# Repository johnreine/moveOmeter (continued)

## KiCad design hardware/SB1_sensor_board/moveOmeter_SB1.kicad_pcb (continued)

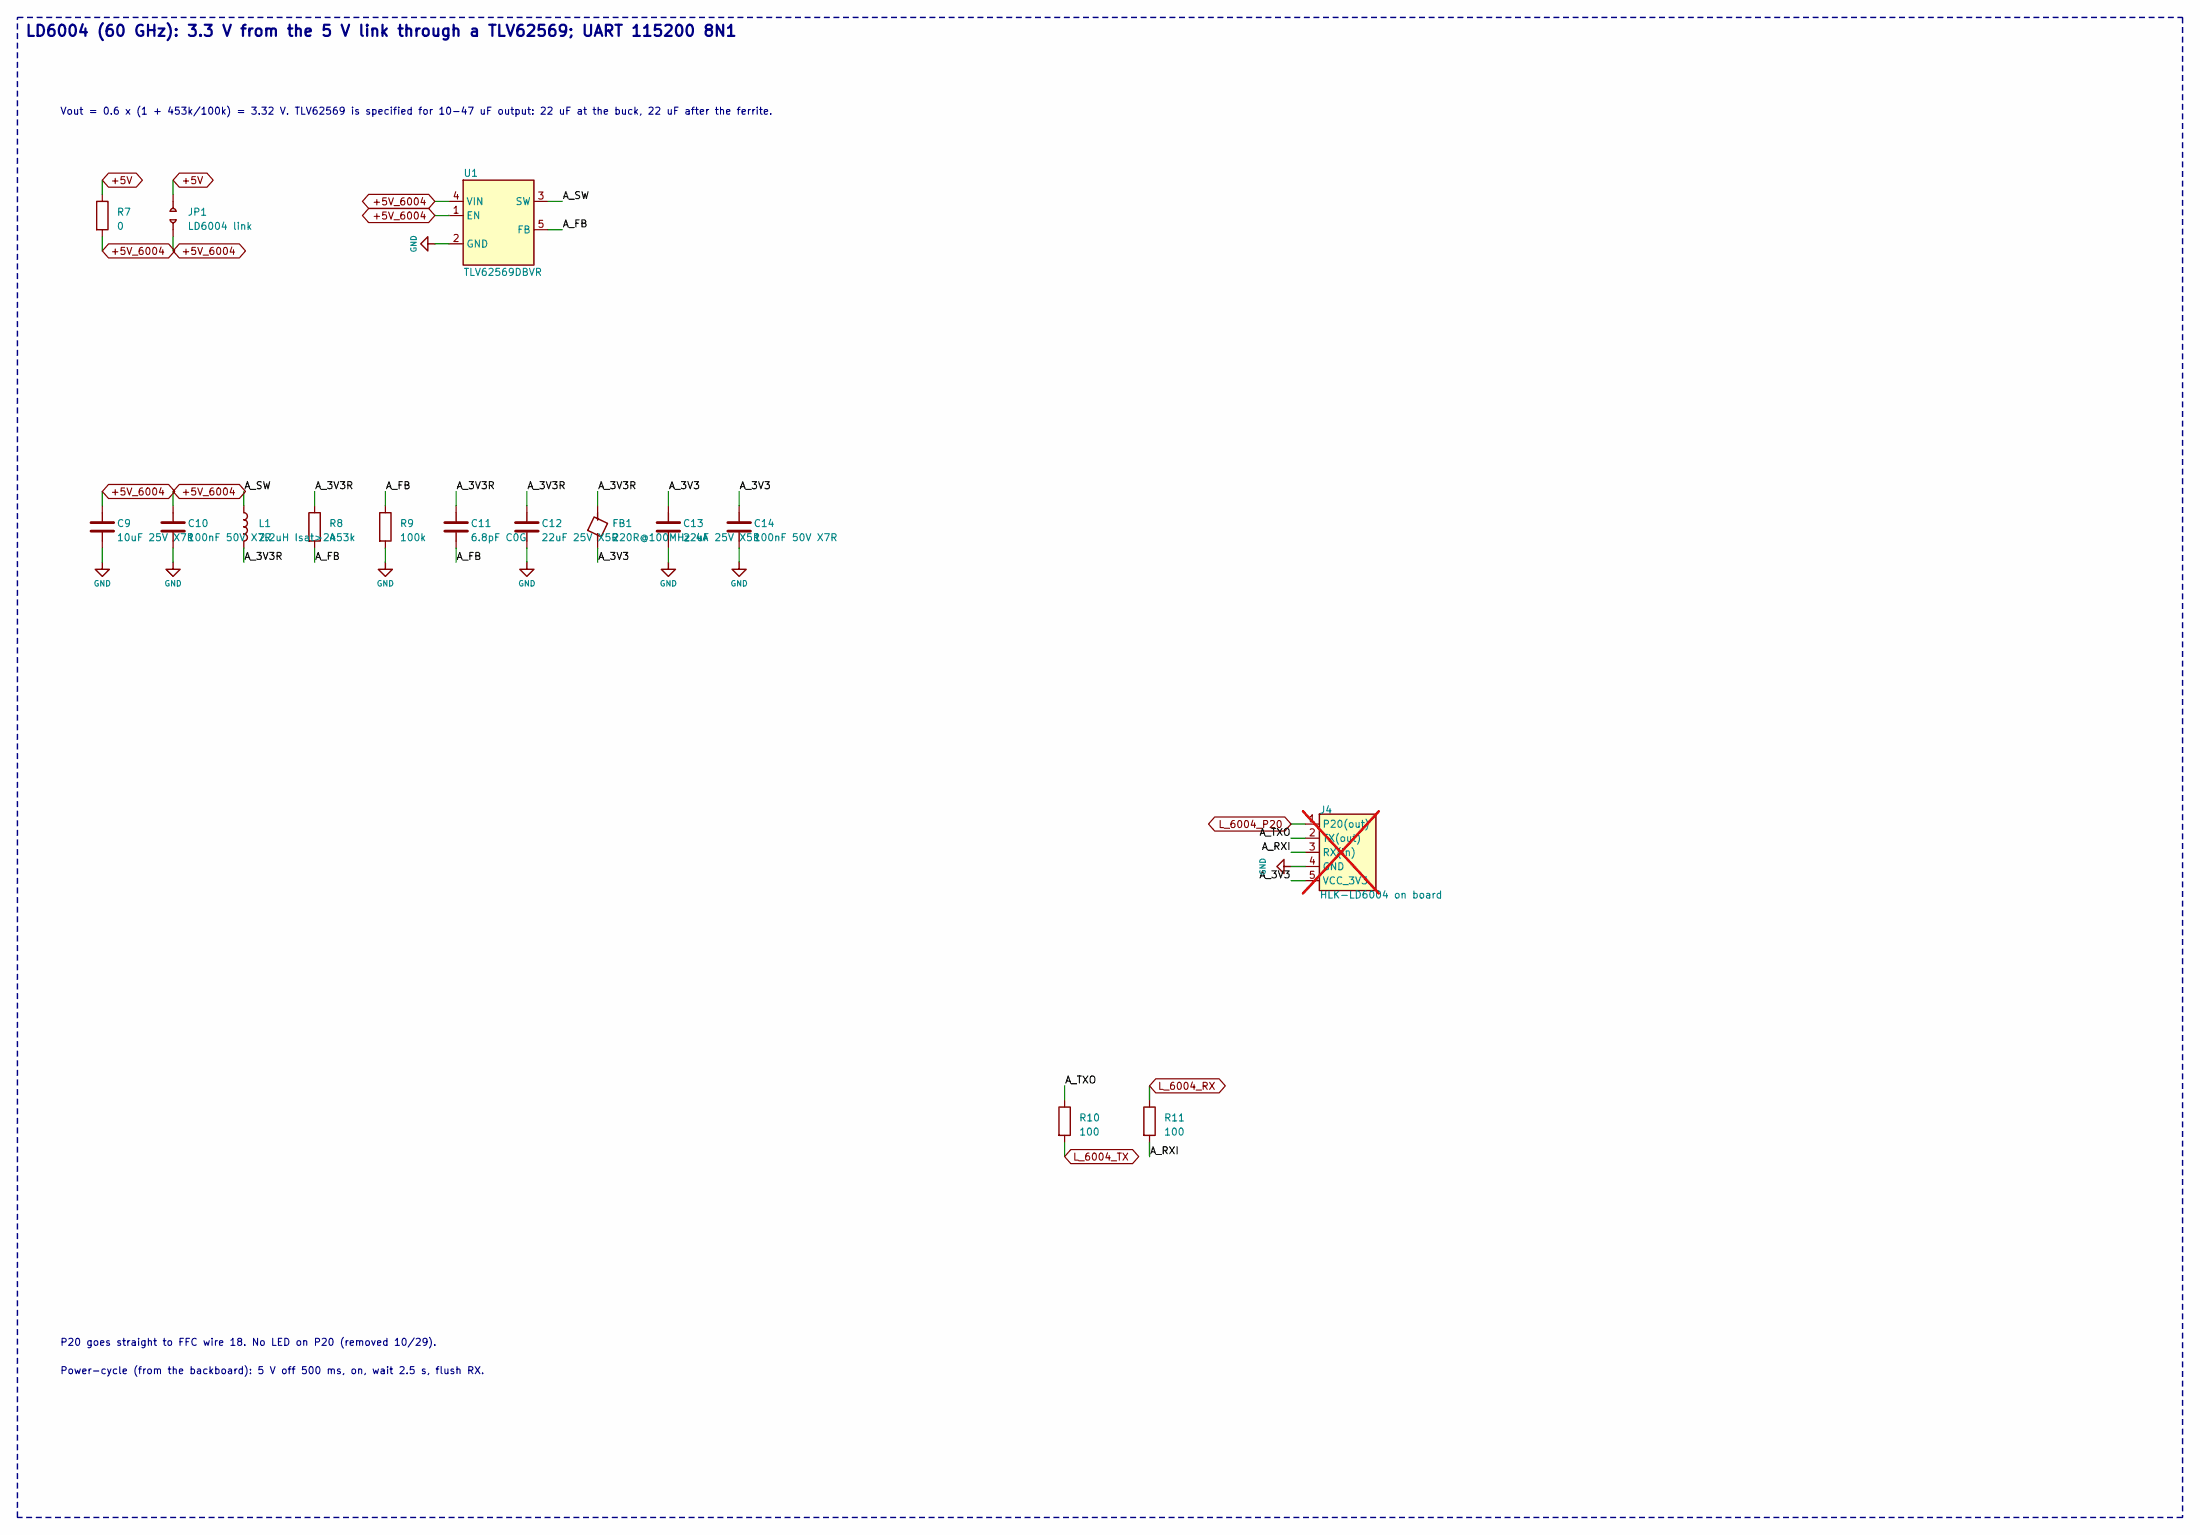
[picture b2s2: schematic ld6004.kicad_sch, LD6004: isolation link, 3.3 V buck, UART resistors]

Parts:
C9: 10uF 25V X7R; C_1210_3225Metric_Pad1.33x2.70mm_HandSolder; MPN GRM32DR71E106KA12L
C10, C14: 100nF 50V X7R; C_1206_3216Metric_Pad1.33x1.80mm_HandSolder; MPN CL31B104KBCNNNC
C11: 6.8pF C0G; C_1206_3216Metric_Pad1.33x1.80mm_HandSolder; MPN CC1206CRNPO9BN6R8
C12, C13: 22uF 25V X5R; C_1210_3225Metric_Pad1.33x2.70mm_HandSolder; MPN GRM32ER61E226KE15L
FB1: 220R@100MHz 4A; L_1206_3216Metric_Pad1.22x1.90mm_HandSolder; MPN LSMGA321616T221NG
J4: HLK-LD6004 on board; HLK-LD6004_Module_2x1x05_P1.27mm; MPN LPPB051NFFN-RC; not fitted
JP1: LD6004 link; SolderJumper-2_P1.3mm_Open_RoundedPad1.0x1.5mm
L1: 2.2uH Isat>2A; L_Bourns-SRN4018; MPN SRN4018-2R2M
R7: 0; R_1206_3216Metric_Pad1.30x1.75mm_HandSolder; MPN RC1206JR-070RL
R8: 453k; R_1206_3216Metric_Pad1.30x1.75mm_HandSolder; MPN RC1206FR-07453KL
R9: 100k; R_1206_3216Metric_Pad1.30x1.75mm_HandSolder; MPN RC1206FR-07100KL
R10, R11: 100; R_1206_3216Metric_Pad1.30x1.75mm_HandSolder; MPN RC1206FR-07100RL
U1: TLV62569DBVR; SOT-23-5; MPN TLV62569DBVR

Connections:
+5V: JP1.1, R7.1; also elsewhere on the board
+5V_6004: C9.1, C10.1, JP1.2, R7.2, U1.1 (EN), U1.4 (VIN)
/LD6004/A_3V3: C13.1, C14.1, FB1.2, J4.5 (VCC_3V3)
/LD6004/A_3V3R: C11.1, C12.1, FB1.1, L1.2, R8.1
/LD6004/A_FB: C11.2, R8.2, R9.1, U1.5 (FB)
/LD6004/A_RXI: J4.3 (RX(in)), R11.2
/LD6004/A_SW: L1.1, U1.3 (SW)
/LD6004/A_TXO: J4.2 (TX(out)), R10.1
GND: C9.2, C10.2, C12.2, C13.2, C14.2, J4.4 (GND), R9.2, U1.2 (GND); also elsewhere on the board
L_6004_P20: J4.1 (P20(out)); also elsewhere on the board
L_6004_RX: R11.1; also elsewhere on the board
L_6004_TX: R10.2; also elsewhere on the board

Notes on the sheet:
LD6004 (60 GHz): 3.3 V from the 5 V link through a TLV62569; UART 115200 8N1
Power-cycle (from the backboard): 5 V off 500 ms, on, wait 2.5 s, flush RX.
Vout = 0.6 x (1 + 453k/100k) = 3.32 V. TLV62569 is specified for 10-47 uF output: 22 uF at the buck, 22 uF after the ferrite.
P20 goes straight to FFC wire 18. No LED on P20 (removed 10/29).

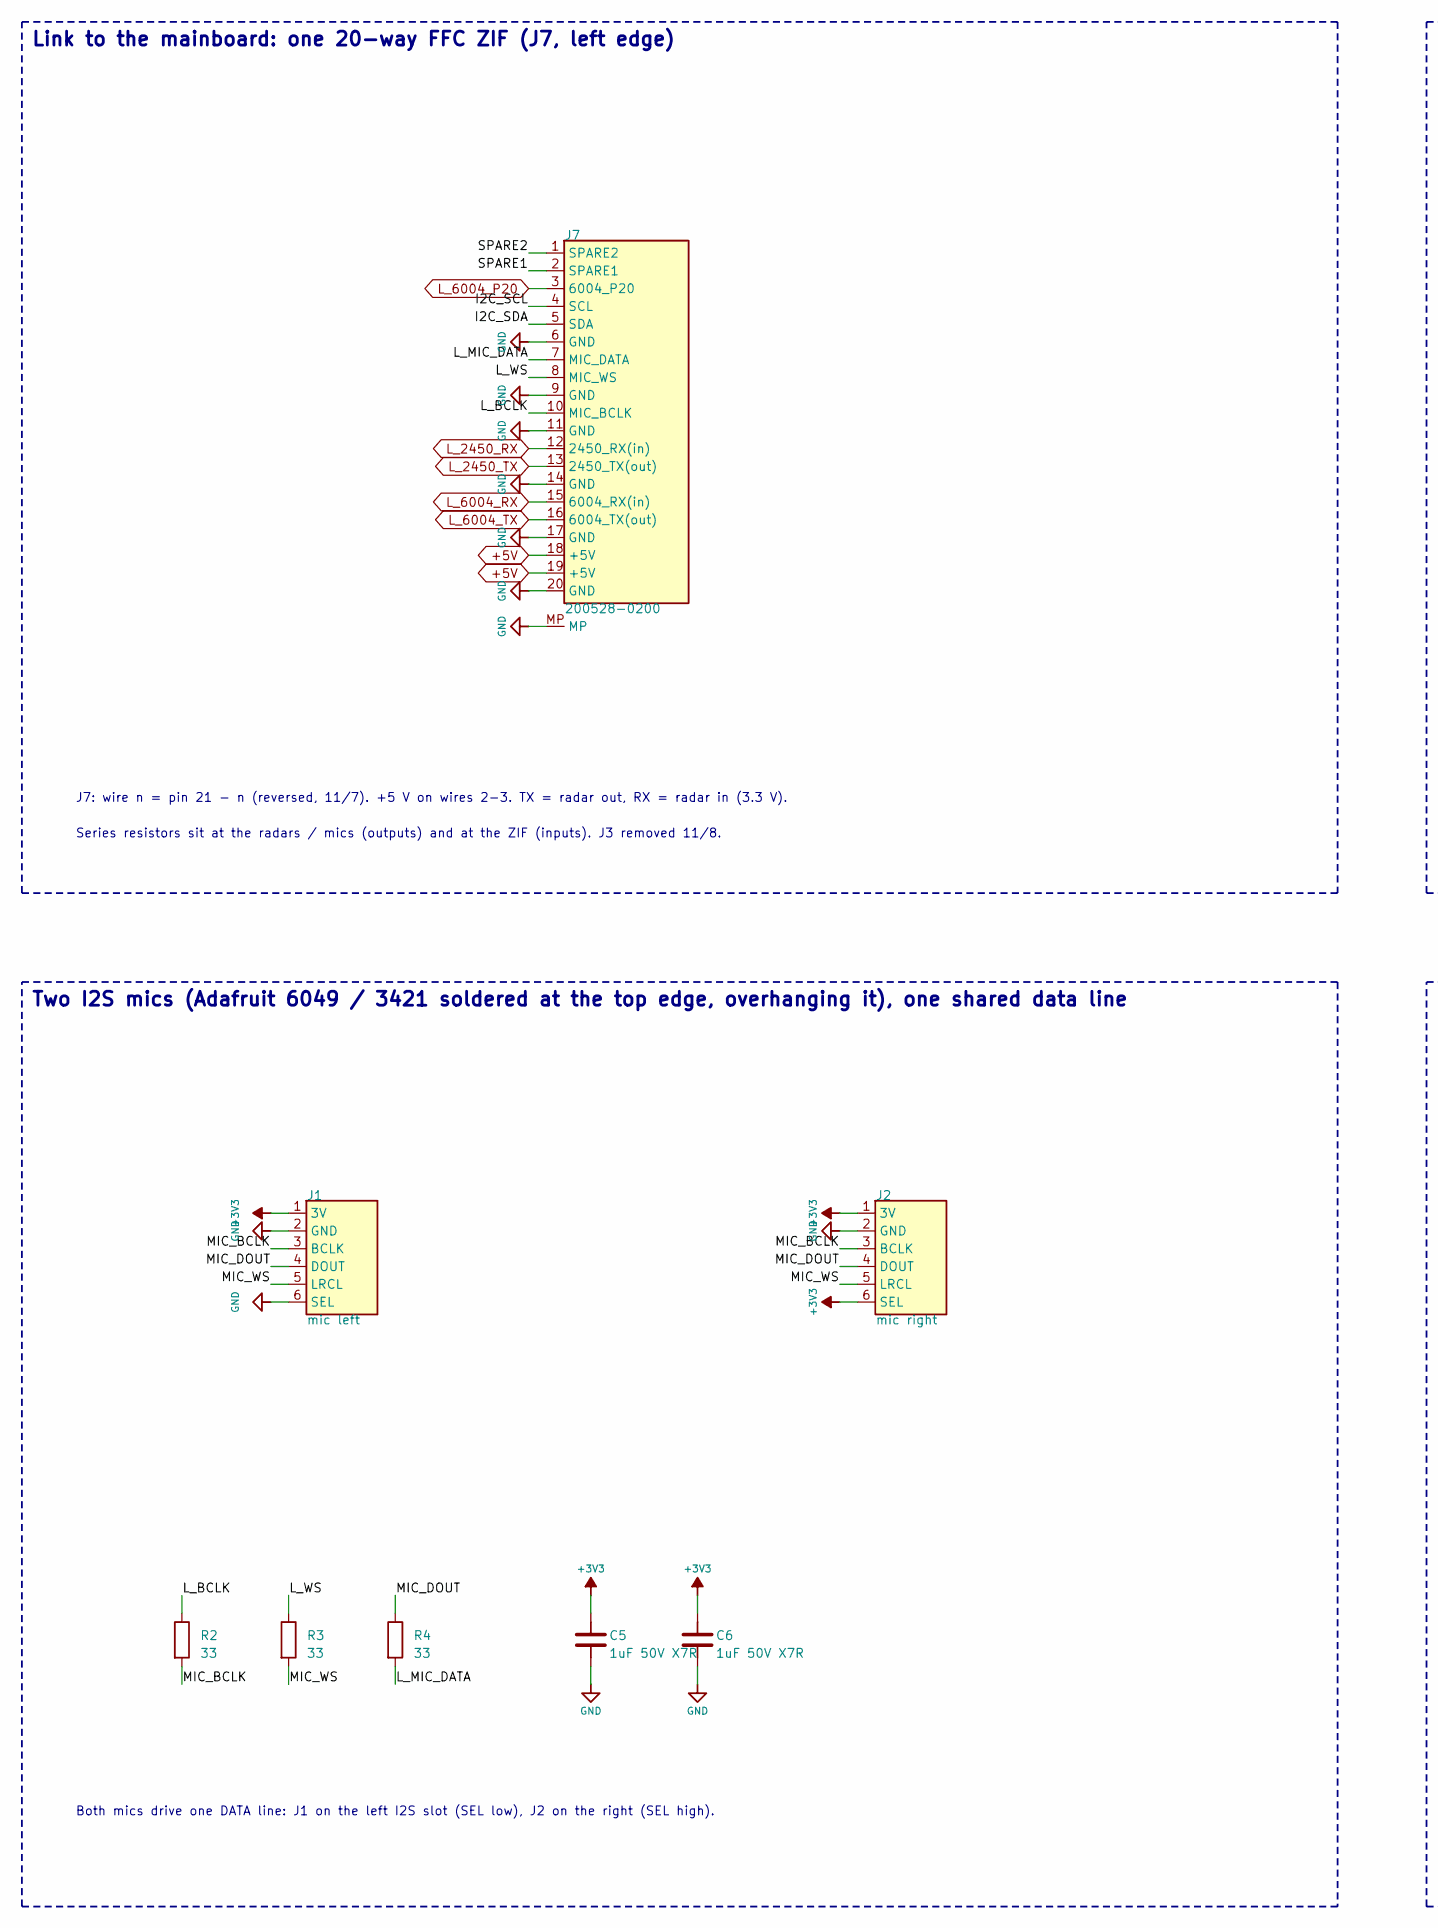
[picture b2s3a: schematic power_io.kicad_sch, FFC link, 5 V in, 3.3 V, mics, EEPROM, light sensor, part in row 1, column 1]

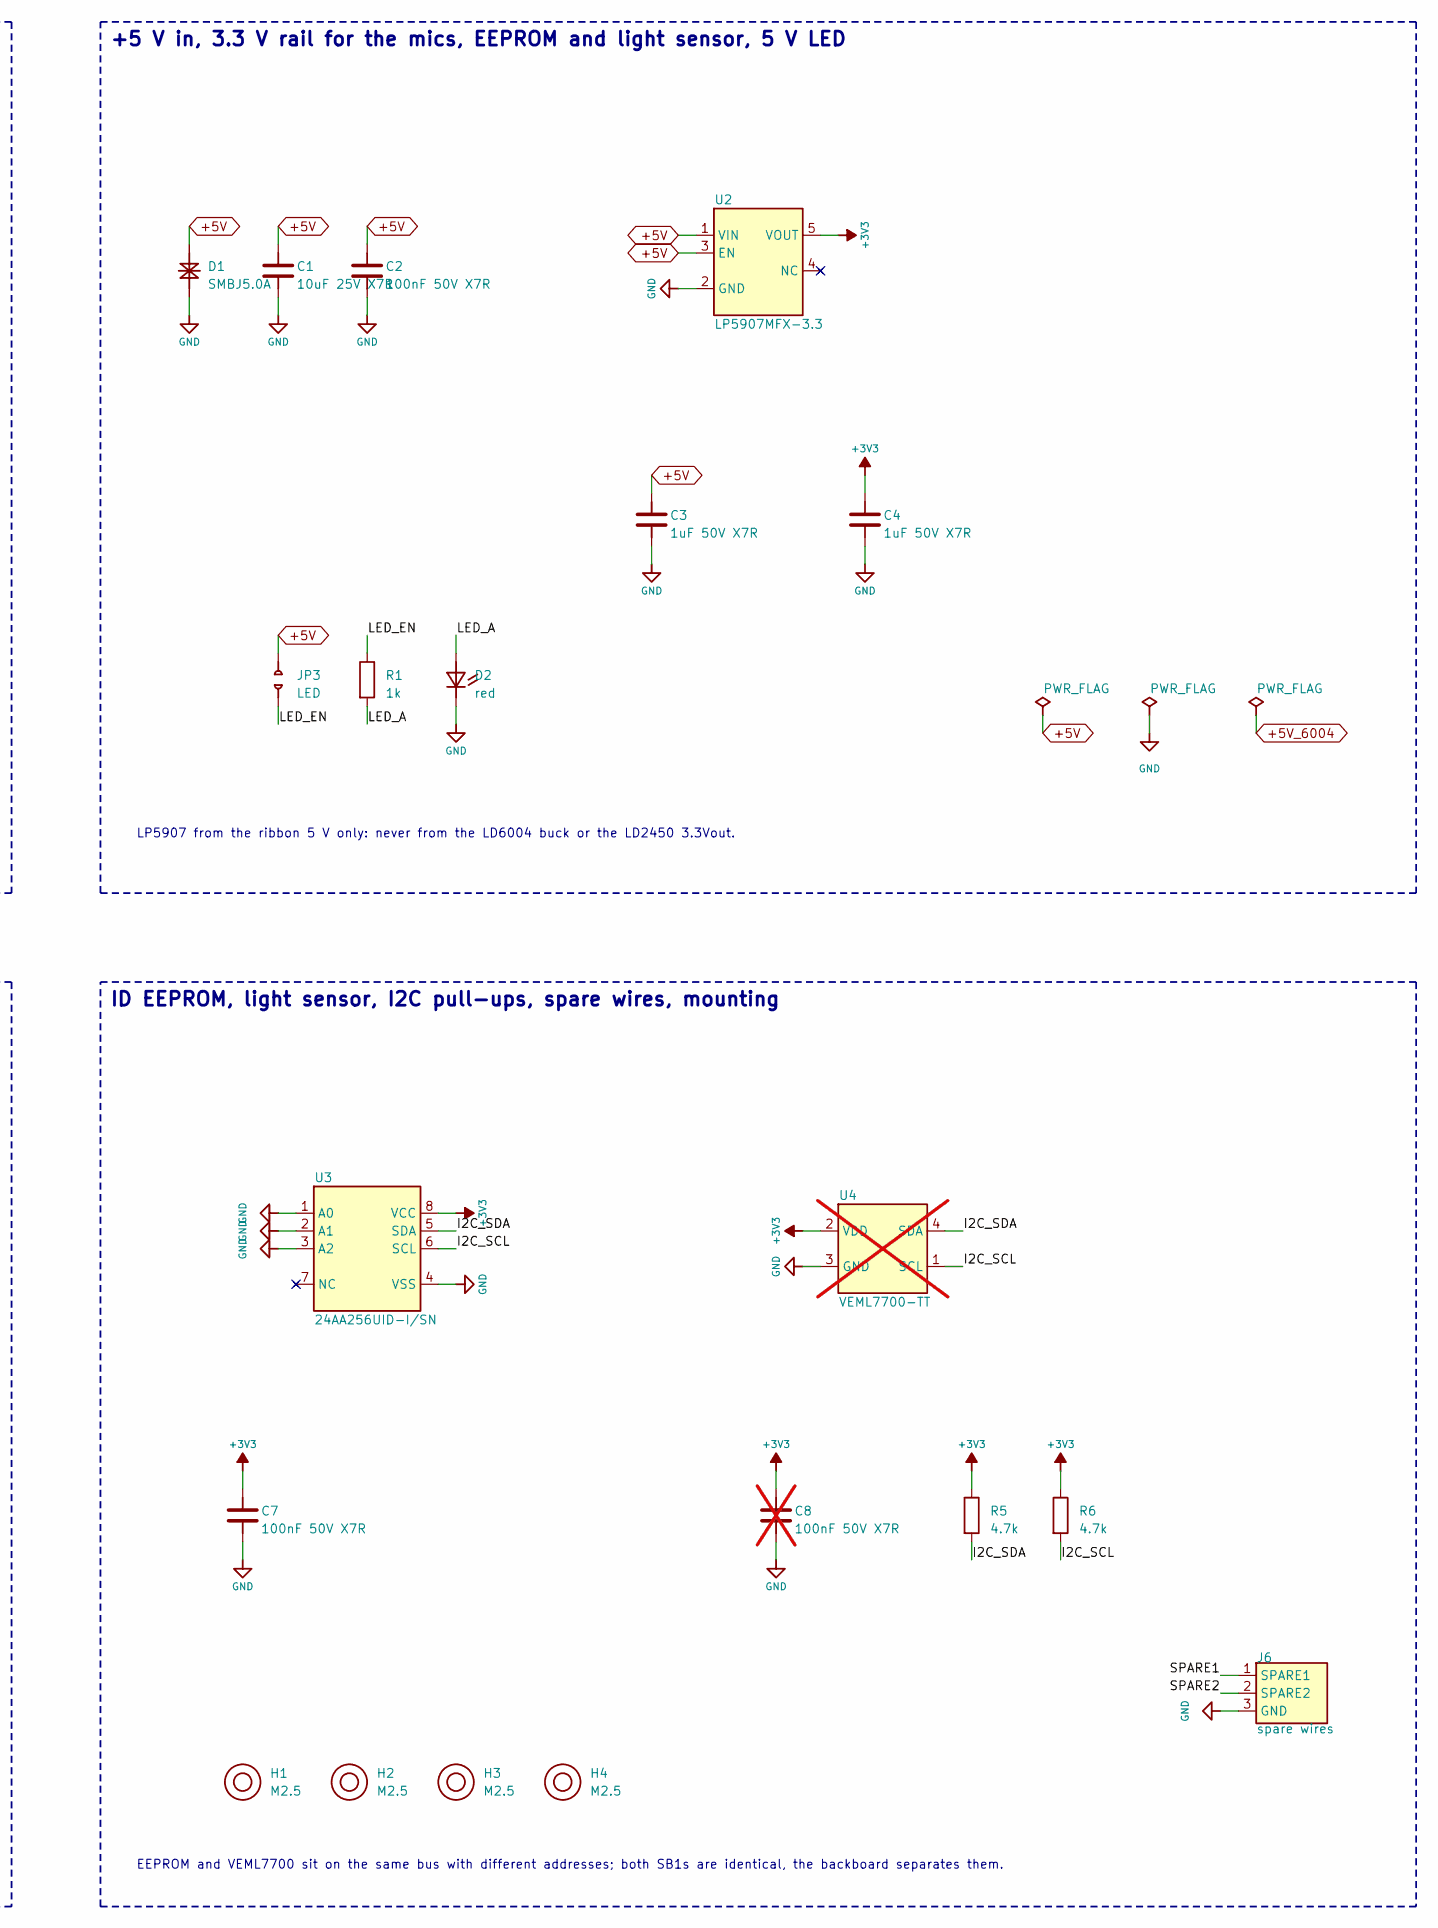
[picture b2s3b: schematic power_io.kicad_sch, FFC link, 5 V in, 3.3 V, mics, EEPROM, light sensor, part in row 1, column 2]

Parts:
C1: 10uF 25V X7R; C_1210_3225Metric_Pad1.33x2.70mm_HandSolder; MPN GRM32DR71E106KA12L
C2, C7: 100nF 50V X7R; C_1206_3216Metric_Pad1.33x1.80mm_HandSolder; MPN CL31B104KBCNNNC
C3, C4, C5, C6: 1uF 50V X7R; C_1206_3216Metric_Pad1.33x1.80mm_HandSolder; MPN CC1206KKX7R9BB105
C8: 100nF 50V X7R; C_1206_3216Metric_Pad1.33x1.80mm_HandSolder; MPN CL31B104KBCNNNC; not fitted
D1: SMBJ5.0A; D_SMB_Handsoldering; MPN SMBJ5.0A
D2: red; LED_1206_3216Metric_Pad1.42x1.75mm_HandSolder; MPN LTST-C150KRKT
H1, H2, H3, H4: M2.5; MountingHole_2.7mm_M2.5_KeepOut
J1: mic left; Adafruit_I2S_Mic_Breakout_1x06_Overhang_Back; MPN 6049
J2: mic right; Adafruit_I2S_Mic_Breakout_1x06_Overhang_Back; MPN 6049
J6: spare wires; PinHeader_1x03_P2.54mm_Vertical; MPN PEC03SAAN
J7: 200528-0200; Molex_200528-0200_1x20-1MP_P1.00mm_Horizontal; MPN 200528-0200
JP3: LED; SolderJumper-2_P1.3mm_Open_RoundedPad1.0x1.5mm
R1: 1k; R_1206_3216Metric_Pad1.30x1.75mm_HandSolder; MPN RC1206FR-071KL
R2, R3, R4: 33; R_1206_3216Metric_Pad1.30x1.75mm_HandSolder; MPN RC1206FR-0733RL
R5, R6: 4.7k; R_1206_3216Metric_Pad1.30x1.75mm_HandSolder; MPN RC1206FR-074K7L
U2: LP5907MFX-3.3; SOT-23-5; MPN LP5907MFX-3.3/NOPB
U3: 24AA256UID-I/SN; SOIC-8_3.9x4.9mm_P1.27mm; MPN 24AA256UID-I/SN
U4: VEML7700-TT; Vishay_VEML7700_TopView; MPN VEML7700-TT; not fitted

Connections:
+3V3: C4.1, C5.1, C6.1, C7.1, C8.1, J1.1 (3V), J2.1 (3V), J2.6 (SEL), R5.1, R6.1, U2.5 (VOUT), U3.8 (VCC), U4.2 (VDD)
+5V: C1.1, C2.1, C3.1, D1.1 (K), J7.18 (+5V), J7.19 (+5V), JP3.1, U2.1 (VIN), U2.3 (EN); also elsewhere on the board
/Power_IO/I2C_SCL: J7.4 (SCL), R6.2, U3.6 (SCL), U4.1 (SCL)
/Power_IO/I2C_SDA: J7.5 (SDA), R5.2, U3.5 (SDA), U4.4 (SDA)
/Power_IO/LED_A: D2.2 (A), R1.2
/Power_IO/LED_EN: JP3.2, R1.1
/Power_IO/L_BCLK: J7.10 (MIC_BCLK), R2.1
/Power_IO/L_MIC_DATA: J7.7 (MIC_DATA), R4.2
/Power_IO/L_WS: J7.8 (MIC_WS), R3.1
/Power_IO/MIC_BCLK: J1.3 (BCLK), J2.3 (BCLK), R2.2
/Power_IO/MIC_DOUT: J1.4 (DOUT), J2.4 (DOUT), R4.1
/Power_IO/MIC_WS: J1.5 (LRCL), J2.5 (LRCL), R3.2
/Power_IO/SPARE1: J6.1 (SPARE1), J7.2 (SPARE1)
/Power_IO/SPARE2: J6.2 (SPARE2), J7.1 (SPARE2)
GND: C1.2, C2.2, C3.2, C4.2, C5.2, C6.2, C7.2, C8.2, D1.2 (A), D2.1 (K), J1.2 (GND), J1.6 (SEL), J2.2 (GND), J6.3 (GND), J7.6 (GND), J7.9 (GND), J7.11 (GND), J7.14 (GND), J7.17 (GND), J7.20 (GND), J7.MP, U2.2 (GND), U3.1 (A0), U3.2 (A1), U3.3 (A2), U3.4 (VSS), U4.3 (GND); also elsewhere on the board
L_2450_RX: J7.12 (2450_RX(in)); also elsewhere on the board
L_2450_TX: J7.13 (2450_TX(out)); also elsewhere on the board
L_6004_P20: J7.3 (6004_P20); also elsewhere on the board
L_6004_RX: J7.15 (6004_RX(in)); also elsewhere on the board
L_6004_TX: J7.16 (6004_TX(out)); also elsewhere on the board

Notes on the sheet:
ID EEPROM, light sensor, I2C pull-ups, spare wires, mounting
LP5907 from the ribbon 5 V only: never from the LD6004 buck or the LD2450 3.3Vout.
EEPROM and VEML7700 sit on the same bus with different addresses; both SB1s are identical, the backboard separates them.
J7: wire n = pin 21 - n (reversed, 11/7). +5 V on wires 2-3. TX = radar out, RX = radar in (3.3 V).
+5 V in, 3.3 V rail for the mics, EEPROM and light sensor, 5 V LED
Series resistors sit at the radars / mics (outputs) and at the ZIF (inputs). J3 removed 11/8.
Both mics drive one DATA line: J1 on the left I2S slot (SEL low), J2 on the right (SEL high).
Two I2S mics (Adafruit 6049 / 3421 soldered at the top edge, overhanging it), one shared data line
Link to the mainboard: one 20-way FFC ZIF (J7, left edge)

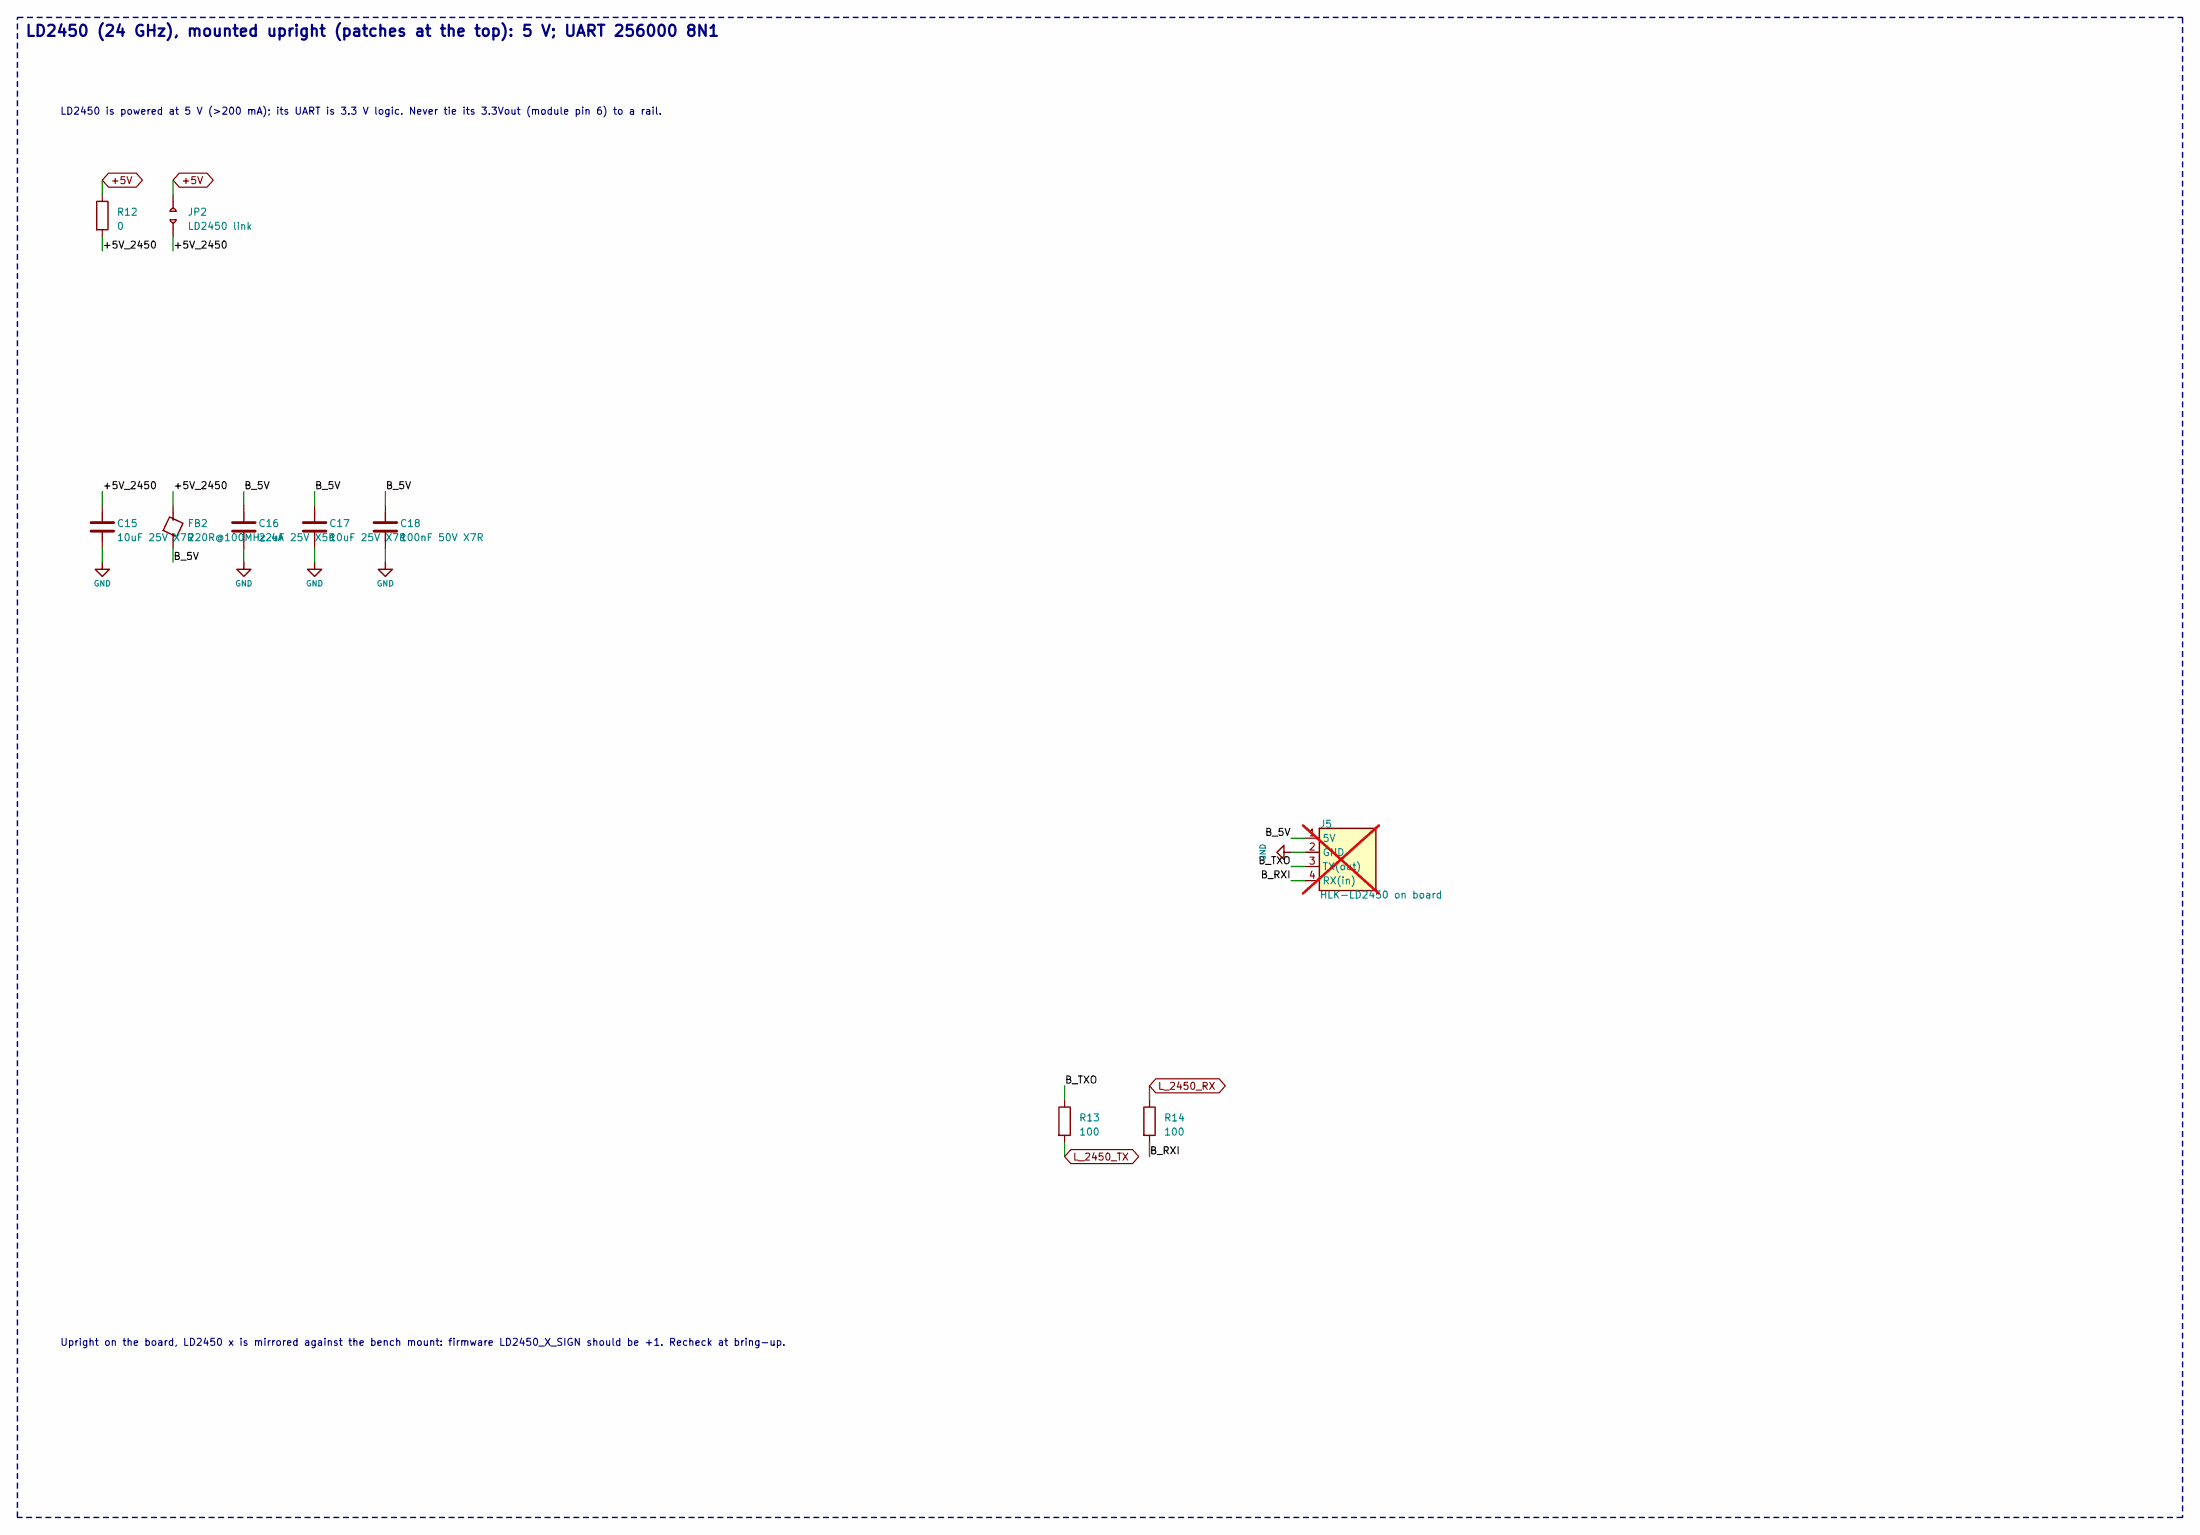
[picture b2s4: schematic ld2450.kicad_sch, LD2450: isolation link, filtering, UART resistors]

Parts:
C15, C17: 10uF 25V X7R; C_1210_3225Metric_Pad1.33x2.70mm_HandSolder; MPN GRM32DR71E106KA12L
C16: 22uF 25V X5R; C_1210_3225Metric_Pad1.33x2.70mm_HandSolder; MPN GRM32ER61E226KE15L
C18: 100nF 50V X7R; C_1206_3216Metric_Pad1.33x1.80mm_HandSolder; MPN CL31B104KBCNNNC
FB2: 220R@100MHz 4A; L_1206_3216Metric_Pad1.22x1.90mm_HandSolder; MPN LSMGA321616T221NG
J5: HLK-LD2450 on board; HLK-LD2450_Module_2x04_P2.00mm; MPN NPPN042AFCN-RC; not fitted
JP2: LD2450 link; SolderJumper-2_P1.3mm_Open_RoundedPad1.0x1.5mm
R12: 0; R_1206_3216Metric_Pad1.30x1.75mm_HandSolder; MPN RC1206JR-070RL
R13, R14: 100; R_1206_3216Metric_Pad1.30x1.75mm_HandSolder; MPN RC1206FR-07100RL

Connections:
+5V: JP2.1, R12.1; also elsewhere on the board
/LD2450/+5V_2450: C15.1, FB2.1, JP2.2, R12.2
/LD2450/B_5V: C16.1, C17.1, C18.1, FB2.2, J5.1 (5V)
/LD2450/B_RXI: J5.4 (RX(in)), R14.2
/LD2450/B_TXO: J5.3 (TX(out)), R13.1
GND: C15.2, C16.2, C17.2, C18.2, J5.2 (GND); also elsewhere on the board
L_2450_RX: R14.1; also elsewhere on the board
L_2450_TX: R13.2; also elsewhere on the board

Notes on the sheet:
LD2450 is powered at 5 V (>200 mA); its UART is 3.3 V logic. Never tie its 3.3Vout (module pin 6) to a rail.
LD2450 (24 GHz), mounted upright (patches at the top): 5 V; UART 256000 8N1
Upright on the board, LD2450 x is mirrored against the bench mount: firmware LD2450_X_SIGN should be +1. Recheck at bring-up.

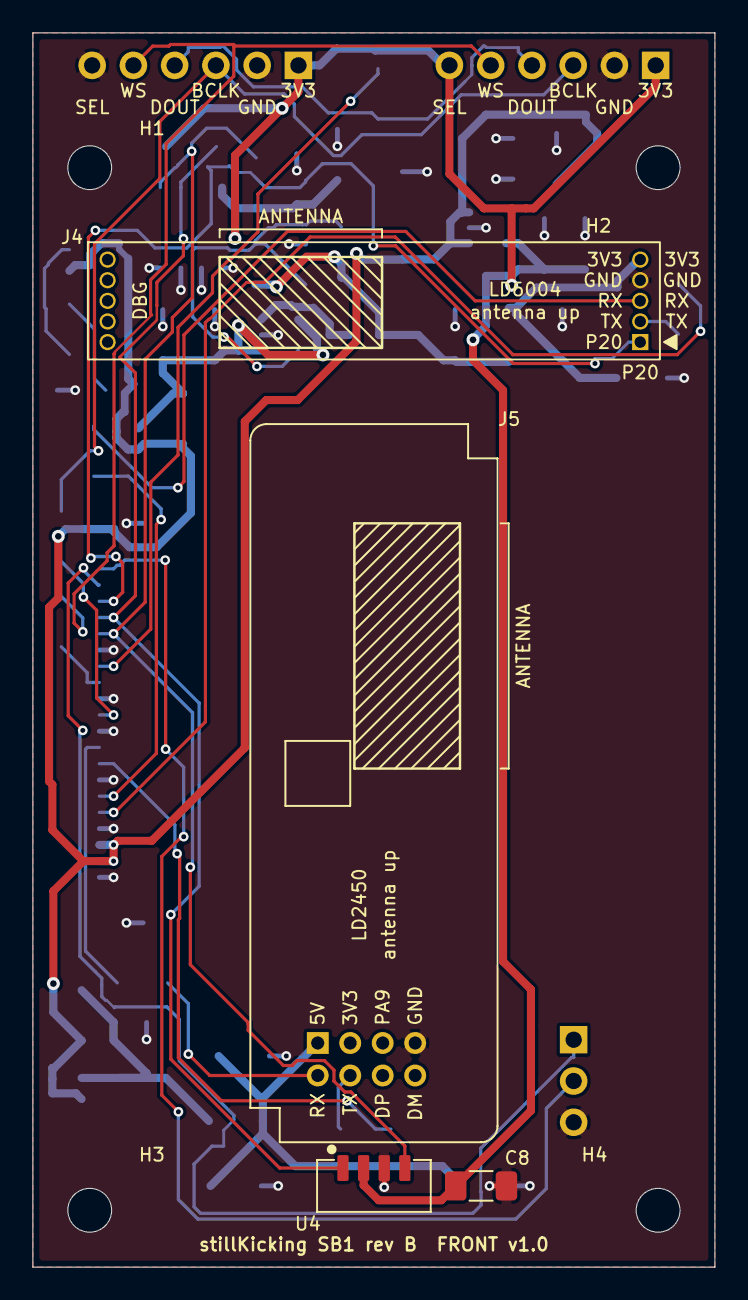
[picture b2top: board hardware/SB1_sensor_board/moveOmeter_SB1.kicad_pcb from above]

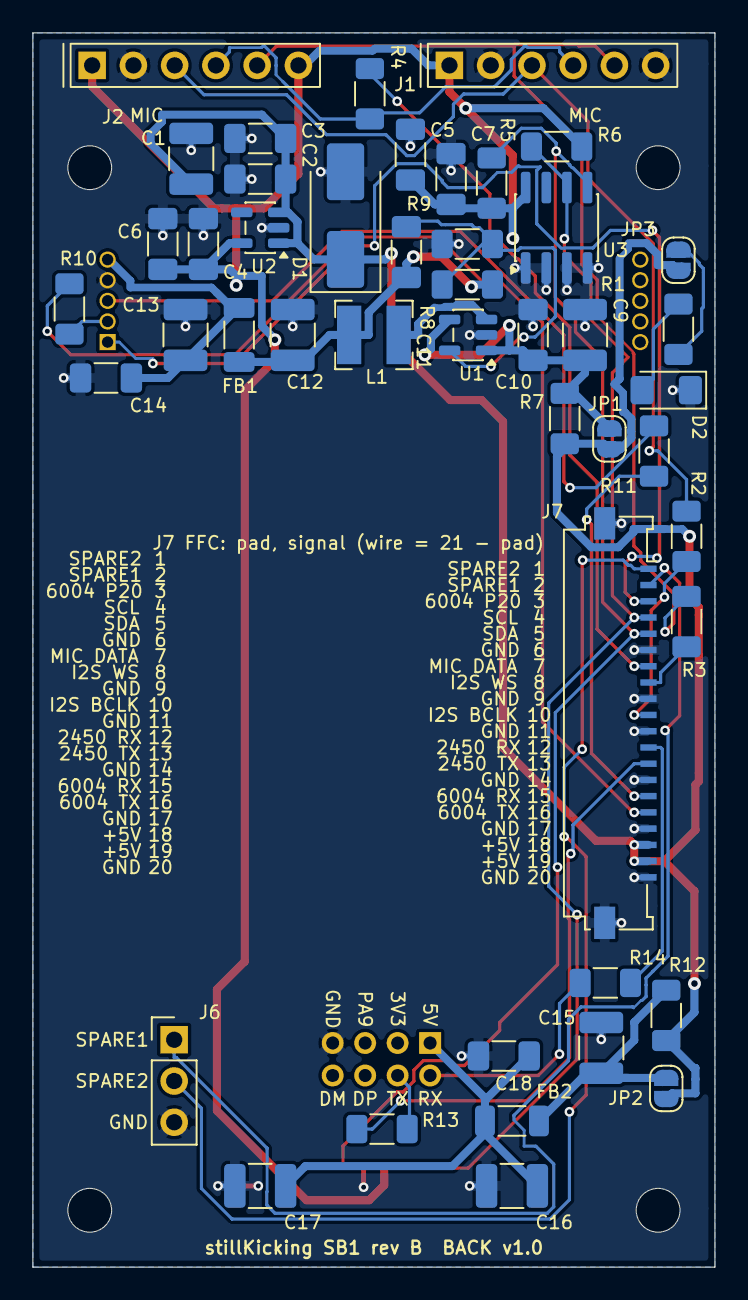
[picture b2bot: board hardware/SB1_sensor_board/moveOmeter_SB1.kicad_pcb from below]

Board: 4 copper layers, 42.0 x 76.0 mm, 54 parts (46 on the bottom side), 31 nets.

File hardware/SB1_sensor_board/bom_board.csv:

Refs,Qty per board,Value,Manufacturer,MPN,Footprint,Fit,Vendor,Vendor Part #,"Price (qty 1, USD)",Ext price per board (USD),Vendor Link,Datasheet
"C1, C9, C15, C17",4,10uF 25V X7R,Murata,GRM32DR71E106KA12L,C_1210_3225Metric_Pad1.33x2.70mm_HandSolder,,DigiKey,490-1867-1-ND,0.98,3.92,https://www.digikey.com/en/products/detail/murata-electronic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,https://pim.murata.com/asset/pim4/ceramicCapacitorSMD/GRM32D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
"C2, C7, C10, C14, C18",5,100nF 50V X7R,Samsung,CL31B104KBCNNNC,C_1206_3216Metric_Pad1.33x1.80mm_HandSolder,,DigiKey,1276-1017-1-ND,0.14,0.7,https://www.digikey.com/en/products/detail/samsung-electro-m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,https://weblib.samsungsem.com/mlcc/mlcc-ec-data-sheet.do?par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
"C3, C4, C5, C6",4,1uF 50V X7R,Yageo,CC1206KKX7R9BB105,C_1206_3216Metric_Pad1.33x1.80mm_HandSolder,,DigiKey,311-1963-1-ND,0.36,1.44,https://www.digikey.com/en/products/detail/yageo/CC1206KKX7R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,https://yageogroup.com/content/datasheet/asset/file/UPY-GPHC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
C8,1,100nF 50V X7R,Samsung,CL31B104KBCNNNC,C_1206_3216Metric_Pad1.33x1.80mm_HandSolder,DNP,DigiKey,1276-1017-1-ND,0.14,,https://www.digikey.com/en/products/detail/samsung-electro-m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,https://weblib.samsungsem.com/mlcc/mlcc-ec-data-sheet.do?par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
C11,1,6.8pF C0G,Yageo,CC1206CRNPO9BN6R8,C_1206_3216Metric_Pad1.33x1.80mm_HandSolder,,DigiKey,311-4367-1-ND,0.31,0.31,https://www.digikey.com/en/products/detail/yageo/CC1206CRNPO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,https://yageogroup.com/download/specsheet/CC1206CRNPO9BN6R8
"C12, C13, C16",3,22uF 25V X5R,Murata,GRM32ER61E226KE15L,C_1210_3225Metric_Pad1.33x2.70mm_HandSolder,,DigiKey,490-3889-1-ND,2.21,6.63,https://www.digikey.com/en/products/detail/murata-electronic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,https://www.mouser.com/datasheet/2/281/1/GRM32ER61E226KE15_0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
D1,1,SMBJ5.0A,Littelfuse,SMBJ5.0A,D_SMB_Handsoldering,,DigiKey,SMBJ5.0ALFCT-ND,0.50,0.5,https://www.digikey.com/en/products/detail/littelfuse-inc/SM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,https://www.littelfuse.com/assetdocs/tvs-diodes-smbj-series-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
D2,1,red,Lite-On,LTST-C150KRKT,LED_1206_3216Metric_Pad1.42x1.75mm_HandSolder,,DigiKey,160-1405-1-ND,0.19,0.19,https://www.digikey.com/en/products/detail/liteon/LTST-C150K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,https://optoelectronics.liteon.com/upload/download/DS-22-99-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
"FB1, FB2",2,220R@100MHz 4A,Taiyo Yuden,LSMGA321616T221NG,L_1206_3216Metric_Pad1.22x1.90mm_HandSolder,,DigiKey,587-LSMGA321616T221NGCT-ND,0.32,0.64,https://www.digikey.com/en/products/detail/taiyo-yuden/LSMGA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,https://mm.digikey.com/Volume0/opasdata/d220001/medias/docus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
J1,1,mic left,Adafruit Industries,6049,Adafruit_I2S_Mic_Breakout_1x06_Overhang_Back,,DigiKey,1528-6049-ND,8.95,8.95,https://www.digikey.com/en/products/detail/adafruit-industri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,https://cdn-shop.adafruit.com/product-files/6049/6049_DS-000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
J2,1,mic right,Adafruit Industries,6049,Adafruit_I2S_Mic_Breakout_1x06_Overhang_Back,,DigiKey,1528-6049-ND,8.95,8.95,https://www.digikey.com/en/products/detail/adafruit-industri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,https://cdn-shop.adafruit.com/product-files/6049/6049_DS-000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
J4,1,HLK-LD6004 on board,Sullins,LPPB051NFFN-RC,HLK-LD6004_Module_2x1x05_P1.27mm,,DigiKey,S9008E-05-ND,0.93,0.93,https://www.digikey.com/en/products/detail/sullins-connector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,https://s3.amazonaws.com/catalogspreads-pdf/PAGE96-97%20.050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
J5,1,HLK-LD2450 on board,Sullins,NPPN042AFCN-RC,HLK-LD2450_Module_2x04_P2.00mm,,DigiKey,S5750-04-ND,1.04,1.04,https://www.digikey.com/en/products/detail/sullins-connector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,https://drawings-pdf.s3.amazonaws.com/10497.pdf
J6,1,spare wires,Sullins,PEC03SAAN,PinHeader_1x03_P2.54mm_Vertical,,DigiKey,35-PEC03SAAN-ND,0.22,0.22,https://www.digikey.com/en/products/detail/sullins-connector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,https://www.sullinscorp.com/catalogs/77_PAGE108-109_.100_MAL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
J7,1,200528-0200,Molex,200528-0200,Molex_200528-0200_1x20-1MP_P1.00mm_Horizontal,,DigiKey,900-2005280200CT-ND,0.89,0.89,https://www.digikey.com/en/products/detail/molex/2005280200/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,https://www.molex.com/en-us/products/part-detail/2005280200
L1,1,2.2uH Isat>2A,Bourns,SRN4018-2R2M,L_Bourns-SRN4018,,DigiKey,SRN4018-2R2MCT-ND,0.40,0.4,https://www.digikey.com/en/products/detail/bourns-inc/SRN401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,https://www.bourns.com/docs/Product-Datasheets/SRN4018.pdf
R1,1,1k,Yageo,RC1206FR-071KL,R_1206_3216Metric_Pad1.30x1.75mm_HandSolder,,DigiKey,311-1.00KFRCT-ND,0.10,0.1,https://www.digikey.com/en/products/detail/yageo/RC1206FR-07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,https://yageogroup.com/content/datasheet/asset/file/PYU-RC_G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
"R2, R3, R4",3,33,Yageo,RC1206FR-0733RL,R_1206_3216Metric_Pad1.30x1.75mm_HandSolder,,DigiKey,311-33.0FRCT-ND,0.11,0.33,https://www.digikey.com/en/products/detail/yageo/RC1206FR-07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,https://yageogroup.com/content/datasheet/asset/file/PYU-RC_G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
"R5, R6",2,4.7k,Yageo,RC1206FR-074K7L,R_1206_3216Metric_Pad1.30x1.75mm_HandSolder,,DigiKey,311-4.70KFRCT-ND,0.11,0.22,https://www.digikey.com/en/products/detail/yageo/RC1206FR-07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,https://yageogroup.com/content/datasheet/asset/file/PYU-RC_G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
"R7, R12",2,0,Yageo,RC1206JR-070RL,R_1206_3216Metric_Pad1.30x1.75mm_HandSolder,,DigiKey,311-0.0ERCT-ND,0.10,0.2,https://www.digikey.com/en/products/detail/yageo/RC1206JR-07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,https://yageogroup.com/content/datasheet/asset/file/PYU-RC_G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
R8,1,453k,Yageo,RC1206FR-07453KL,R_1206_3216Metric_Pad1.30x1.75mm_HandSolder,,DigiKey,311-453KFRCT-ND,0.11,0.11,https://www.digikey.com/en/products/detail/yageo/RC1206FR-07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,https://yageogroup.com/content/datasheet/asset/file/PYU-RC_G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
R9,1,100k,Yageo,RC1206FR-07100KL,R_1206_3216Metric_Pad1.30x1.75mm_HandSolder,,DigiKey,311-100KFRCT-ND,0.11,0.11,https://www.digikey.com/en/products/detail/yageo/RC1206FR-07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,https://yageogroup.com/content/datasheet/asset/file/PYU-RC_G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
"R10, R11, R13, R14",4,100,Yageo,RC1206FR-07100RL,R_1206_3216Metric_Pad1.30x1.75mm_HandSolder,,DigiKey,311-100FRCT-ND,0.11,0.44,https://www.digikey.com/en/products/detail/yageo/RC1206FR-07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,https://yageogroup.com/content/datasheet/asset/file/PYU-RC_G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
U1,1,TLV62569DBVR,TI,TLV62569DBVR,SOT-23-5,,DigiKey,296-47360-1-ND,0.28,0.28,https://www.digikey.com/en/products/detail/texas-instruments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,https://www.ti.com/lit/ds/symlink/tlv62569.pdf
U2,1,LP5907MFX-3.3,TI,LP5907MFX-3.3/NOPB,SOT-23-5,,DigiKey,296-38557-1-ND,0.66,0.66,https://www.digikey.com/en/products/detail/texas-instruments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,https://www.ti.com/lit/ds/symlink/lp5907.pdf
U3,1,24AA256UID-I/SN,Microchip,24AA256UID-I/SN,SOIC-8_3.9x4.9mm_P1.27mm,,DigiKey,24AA256UID-I/SN-ND,1.10,1.1,https://www.digikey.com/en/products/detail/microchip-technol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,https://ww1.microchip.com/downloads/en/DeviceDoc/20005202A.pdf
U4,1,VEML7700-TT,Vishay,VEML7700-TT,Vishay_VEML7700_TopView,DNP,DigiKey,751-VEML7700-TTCT-ND,1.44,,https://www.digikey.com/en/products/detail/vishay-semiconduc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,https://www.vishay.com/docs/84286/veml7700.pdf
(with J4),1,,Sullins,LPPB051NFFN-RC,,,DigiKey,S9008E-05-ND,0.93,0.93,https://www.digikey.com/en/products/detail/sullins-connector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,https://s3.amazonaws.com/catalogspreads-pdf/PAGE96-97%20.050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
(with J4),2,,Sullins,GRPB051VWVN-RC,,,DigiKey,S9014E-05-ND,0.35,0.7,https://www.digikey.com/en/products/detail/sullins-connector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,https://s3.amazonaws.com/catalogspreads-pdf/PAGE94-95%20.050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

"Total per board at qty-1 prices (fitted parts, sockets and shunts included)",,,,,,,,,,40.89,,
"Prices: DigiKey qty-1 unit prices in USD, every SB1 line checked on digikey.com 2026-11-10 (stock and price move daily: recheck before ordering)",,,,,,,,,,,,
